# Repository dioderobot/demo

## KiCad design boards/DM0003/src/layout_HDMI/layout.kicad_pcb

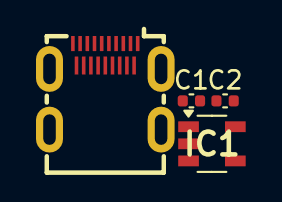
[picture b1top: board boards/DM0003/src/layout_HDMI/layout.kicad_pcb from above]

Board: 2 copper layers, 4 parts (0 on the bottom side), 3 nets, no tracks yet.

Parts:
C1, C2: GCM155R71H104KE02D; C_0402_1005Metric
IC1: STMPS2151STR; SOT95P280X145-5N
USB1: 685119248123; HDMI-SMD_HDMI-101S

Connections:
5V: C1.1, IC1.4, IC1.5
GND: C1.2, C2.2, IC1.2, USB1.4, USB1.7, USB1.10, USB1.13, USB1.16, USB1.20
HDMI_5V: C2.1, IC1.1, USB1.19

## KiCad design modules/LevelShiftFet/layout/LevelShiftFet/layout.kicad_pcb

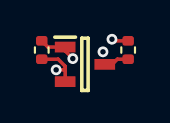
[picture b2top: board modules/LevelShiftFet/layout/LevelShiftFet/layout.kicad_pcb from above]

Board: 2 copper layers, 3 parts (0 on the bottom side), 3 nets.

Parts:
Q1: BSS138-7-F; SOT96P240X115-3N
R1, R2: ERJ-2RKF1002X; R_0402_1005Metric

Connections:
POWER_LOWER: Q1.1, R2.1
SIGNAL_LOWER: Q1.2, R2.2
SIGNAL_UPPER: Q1.3, R1.2

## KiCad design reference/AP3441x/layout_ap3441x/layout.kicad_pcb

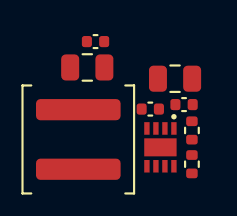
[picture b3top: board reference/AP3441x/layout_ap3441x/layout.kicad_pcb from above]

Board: 2 copper layers, 9 parts (0 on the bottom side), 5 nets, no tracks yet.

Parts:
C1: GRM155R71H472KA01D; C_0402_1005Metric
C2, C4: GRM21BZ71E106KE15K; C_0805_2012Metric
C3, C5: GCM155R71H104KE02D; C_0402_1005Metric
IC1: AP3441SHE-7B; SON50P201X201X60-9N-D
L1: XAL5030-222MEC; L_Coilcraft_XAL5030-XXX
R1: ERJ-2RKF1002X; R_0402_1005Metric
R2: ERJ-2RKF4532X; R_0402_1005Metric

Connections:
FB_NODE: C1.2, IC1.1, R1.1, R2.2
GND: C2.2, C3.2, C4.2, C5.2, IC1.4, IC1.8, IC1.9, R1.2
LX_OUT: IC1.6, L1.1
VIN: C2.1, C3.1, IC1.3
VOUT: C1.1, C4.1, C5.1, L1.2, R2.1

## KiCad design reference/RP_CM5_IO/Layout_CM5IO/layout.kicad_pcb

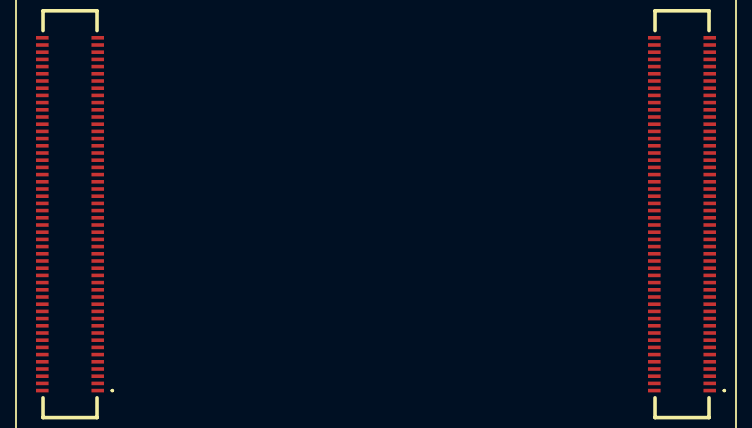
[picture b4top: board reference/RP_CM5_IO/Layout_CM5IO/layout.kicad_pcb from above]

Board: 2 copper layers, 6 parts (0 on the bottom side), 4 nets, no tracks yet.

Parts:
H1, H2, H3, H4: M2.5 DIN965 Mechanical; MountingHole_2.7mm_M2.5_DIN965
J1, J2: 10164227-1001A1RLF; 101642271001A1RLF

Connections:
GND: J1.1, J1.2, J1.7, J1.8, J1.13, J1.14, J1.22, J1.23, J1.32, J1.33, J1.42, J1.43, J1.52, J1.53, J1.59, J1.60, J1.65, J1.66, J1.71, J1.74, J1.98, J2.7, J2.8, J2.13, J2.14, J2.19, J2.20, J2.25, J2.26, J2.31, J2.32, J2.37, J2.38, J2.44, J2.50, J2.55, J2.56, J2.61, J2.62, J2.67, J2.68, J2.73, J2.74, J2.79, J2.80, J2.85, J2.86, J2.91, J2.92, J2.97, J2.98
V1V8_OUTPUT: J1.88, J1.90
V3V3_OUTPUT: J1.84, J1.86
V5V_INPUT: J1.77, J1.79, J1.81, J1.83, J1.85, J1.87

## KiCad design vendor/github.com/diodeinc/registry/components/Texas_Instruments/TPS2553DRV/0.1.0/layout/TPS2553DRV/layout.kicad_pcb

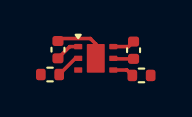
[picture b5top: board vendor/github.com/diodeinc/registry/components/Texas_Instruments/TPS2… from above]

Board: 2 copper layers, 5 parts (0 on the bottom side), 5 nets.

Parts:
C1, C2: GRM155Z71A105KE01D; C_0402_1005Metric
R1: ERJ-2RKF1003X; R_0402_1005Metric
R2: ERJ-2RKF4322X; R_0402_1005Metric
U1: TPS2553DRVR; TPS2553DRV

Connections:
EN: R1.1, U1.4
GND: C1.2, C2.2, R2.2, U1.5, U1.7
VIN: C1.1, R1.2, U1.6
VOUT: C2.1, U1.1
_ILIM: R2.1, U1.2

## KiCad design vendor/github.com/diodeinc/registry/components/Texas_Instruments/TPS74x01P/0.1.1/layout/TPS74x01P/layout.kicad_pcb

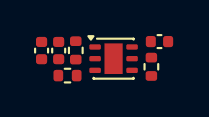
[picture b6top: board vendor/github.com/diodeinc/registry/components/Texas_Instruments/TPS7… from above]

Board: 2 copper layers, 7 parts (0 on the bottom side), 5 nets, no tracks yet.

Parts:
C1: GRM1555CYA103GE01D; C_0402_1005Metric
C2, C3: GRM155Z71A105KE01D; C_0402_1005Metric
R1: ERJ-2RKF1003X; R_0402_1005Metric
R2: ERJ-2RKF5102X; R_0402_1005Metric
R3: ERJ-2RKF2553X; R_0402_1005Metric
U1: TPS74501PDRVR; TPS74x01P

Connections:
EN: R1.2, U1.4
GND: C2.2, C3.2, R2.2, U1.3, U1.7
VIN: C2.1, R1.1, U1.6
VOUT: C1.1, C3.1, R3.1, U1.1
_FB: C1.2, R2.1, R3.2, U1.2

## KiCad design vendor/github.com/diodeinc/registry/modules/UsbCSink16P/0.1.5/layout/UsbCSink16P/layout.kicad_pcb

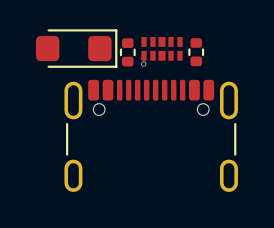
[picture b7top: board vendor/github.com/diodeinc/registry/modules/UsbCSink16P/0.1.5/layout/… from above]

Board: 2 copper layers, 5 parts (0 on the bottom side), 6 nets, no tracks yet.

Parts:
D1: SMF5V0A-E3-08; D_SMF
IC1: TPD4E05U06QDQARQ1; DQA_R-PUSON-N10_
J1: USB4105-GF-A; USB_C_Receptacle_GCT_USB4105-xx-A_16P_TopMnt_Horizontal
R1, R2: ERJ-2RKF5101X; R_0402_1005Metric

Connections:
GND: D1.2, IC1.3, IC1.8, J1.A1, J1.A12, J1.B1, J1.B12, J1.S1, R1.2, R2.2
USB_C_CC1: IC1.1, IC1.10, J1.A5, R1.1
USB_C_CC2: IC1.5, IC1.6, J1.B5, R2.1
USB_C_D_N: IC1.2, IC1.9, J1.A7, J1.B7
USB_C_D_P: IC1.4, IC1.7, J1.A6, J1.B6
VBUS: D1.1, J1.A4, J1.A9, J1.B4, J1.B9
